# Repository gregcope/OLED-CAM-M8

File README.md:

# OLED-CAM-M8
OLED / NEO CAM M8Q Board is designed to go above other boards so that;
1. The GNS has a large ground plane for its internal attenna
2. The GNS has nothing near its antenna so that it has a good view of the sky
3. The OLED is ontop

More to follow... if it works

# Version
1. OLED-CAM-M8_2019-11-25.zip sent to fab

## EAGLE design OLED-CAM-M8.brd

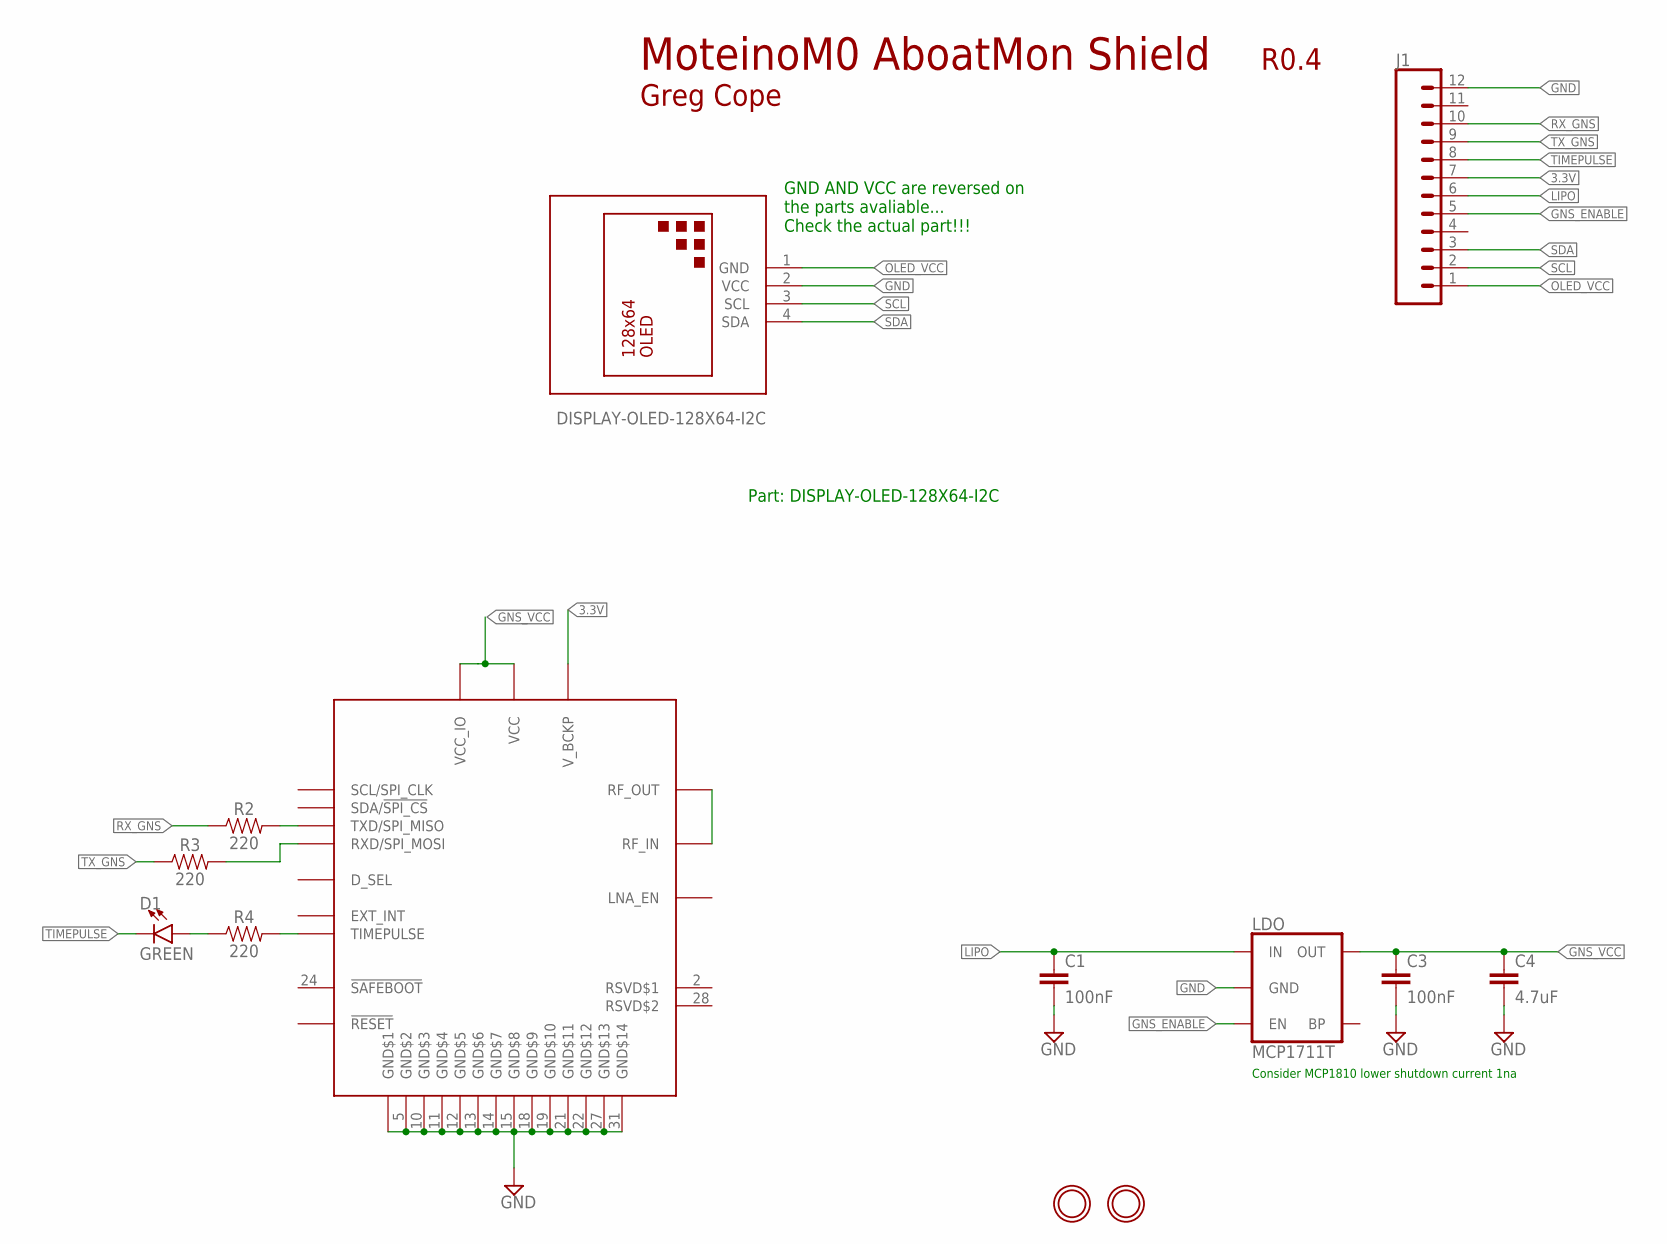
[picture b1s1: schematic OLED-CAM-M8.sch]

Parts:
C1, C3: 100nF; 0603
C4: 4.7uF; 0603
D1: GREEN; LED-0603
GND: MOUNTINGHOLE2.5; MOUNTINGHOLE_2.5_PLATED
J1: CONN_12; 1X12
LDO: MCP1711T; SOT23-5
R2, R3, R4: 220; 0603
U$2: DISPLAY-OLED-128X64-I2C
U$5: CAM-M8
U$7: MOUNTINGHOLE2.5; MOUNTINGHOLE_2.5_PLATED

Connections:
3.3V: J1.7, U$5.8 (V_BCKP)
GND: C1.2, C3.2, C4.2, J1.12, LDO.2 (GND), U$2.2 (VCC), U$5.4 (GND$1), U$5.5 (GND$2), U$5.10 (GND$3), U$5.11 (GND$4), U$5.12 (GND$5), U$5.13 (GND$6), U$5.14 (GND$7), U$5.15 (GND$8), U$5.18 (GND$9), U$5.19 (GND$10), U$5.21 (GND$11), U$5.22 (GND$12), U$5.27 (GND$13), U$5.31 (GND$14)
GNS_ENABLE: J1.5, LDO.3 (EN)
GNS_VCC: C3.1, C4.1, LDO.5 (OUT), U$5.1 (VCC_IO), U$5.9 (VCC)
LIPO: C1.1, J1.6, LDO.1 (IN)
unnamed: R4.2, U$5.29 (TIMEPULSE)
unnamed: R2.2, U$5.25 (TXD/SPI_MISO)
unnamed: R3.2, U$5.26 (RXD/SPI_MOSI)
unnamed: D1.A, R4.1
unnamed: U$5.16 (RF_OUT), U$5.17 (RF_IN)
OLED_VCC: J1.1, U$2.1 (GND)
RX_GNS: J1.10, R2.1
SCL: J1.2, U$2.3 (SCL)
SDA: J1.3, U$2.4 (SDA)
TIMEPULSE: D1.C, J1.8
TX_GNS: J1.9, R3.1

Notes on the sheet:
Greg Cope
R0.4
MoteinoM0 AboatMon Shield
Consider MCP1810 lower shutdown current 1na
Part: DISPLAY-OLED-128X64-I2C
GND AND VCC are reversed on the parts avaliable... Check the actual part!!!

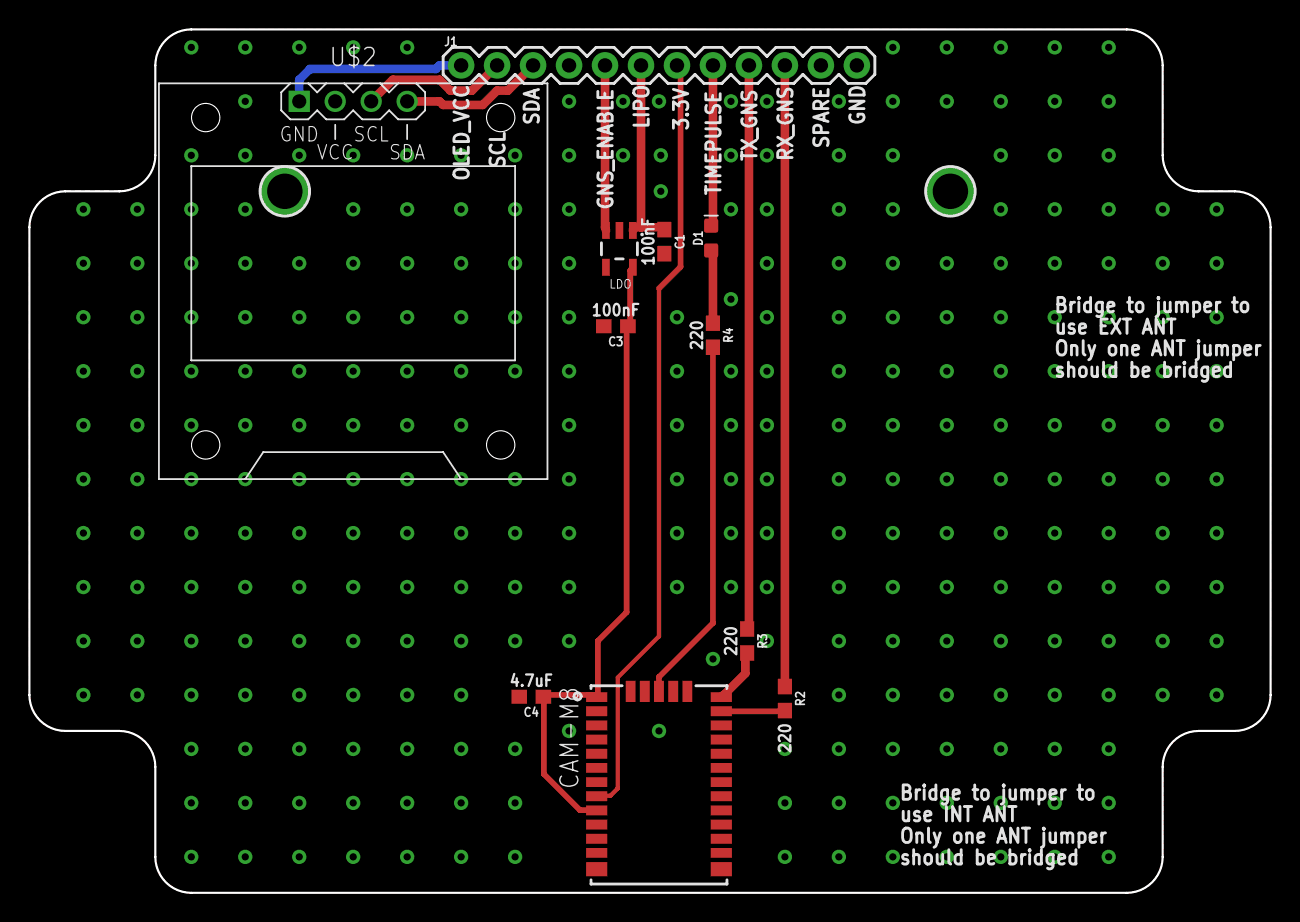
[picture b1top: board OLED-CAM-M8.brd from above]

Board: 2 copper layers, 87.6 x 61.0 mm, 13 parts (0 on the bottom side), 16 nets.

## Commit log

2019-11-25 DRC, ERC pass
2019-11-25 Readme update
2019-11-25 Added GND vias and notes
2019-11-25 Added mounting hole
2019-11-25 added zip
2019-11-26 Sent to fab
2019-12-08 Swapped VCC GND
2019-12-08 removed mounting hole and moved 100n cap
2019-12-08 moved 3v rail
2019-12-08 removed ufl and jumpers

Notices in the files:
parts and their libraries:
SparkFun-Connectors: Licensing: Creative Commons ShareAlike 4.0 International - https://creativecommons.org/licenses/by-sa/4.0
diy-modules: Released under the Creative Commons Attribution 4.0 International License: http://creativecommons.org/licenses/by/4.0
